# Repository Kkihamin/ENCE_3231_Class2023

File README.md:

# ENCE_3231_Class2023 Phase D

## Introduction of Project
  The inspiration initially for the final project in this class was I was researching on the internet for ideas on projects that are beneficial in my daily life and achievable in three weeks even if there are complications during the process of the project. Then, I came across a fridge alarm circuit on the internet and I thought this was a good project idea that was not too difficult to achieve in three weeks and this project could be meaningful because if someone forgets to close there refridgerator this circuit could tell them through a sound from a buzzer that the refridgerator door is open.
  The original circuit that internet provided which is given below was way too complex for three weeks because there were some challenges of implementing the original circuit. First, it was implemented on Arduino instead of the stm32cubeide that I needed to use. Second, there were two timer ic chips which it would take some time to understand to incorporate in the ide. Third, the 9 volts needed for the ic chips are not able to be provided by the voltage on the stm32F4 discovery board and I did not know how to interface a battery with the STM32F4 discovery board. This is why I made the project simplier to be able to accomplish the project in three weeks.

## Components

| Components | Quantity |
| ------------- | ------------- |
| AST-030C0MR-R passive Buzzer  | 1  |
| Green LED  | 1  |
| 100 ohm resistor  | 1 |
| STM32F discovery board  | 1  |
| HRC-SR501 Motion Sensor | 1  |

The table above shows all the components used in my final project which is the Fridge Alarm system.

## Schematic
Below is the Schematic and flowchart of the code on paper the only thing that needs to change is the buzzer should be using pin PE9 instead of PB11 and there is no Timer2:

The Schematic of the Fridge Alarm is shown in Kicad below:

## Shield Development
Below I have included a picture of the shield for my fridge door alarm routed and in 3-D view. The only thing is that I created my own library for the HRC-SR501 motion sensor so the pins on the custom component in my custom library and at first I didn't know why they were not routing and figured out that the pins needed pin numbers so they can actually route.

## Software Development
The main code for the Fridge door alarm is listed below

'''int main(void){
    HAL_Init();
    SystemClock_Config();
     MX_GPIO_Init();
     MX_TIM1_Init();
     MX_TIM2_Init();
     MX_BUZZER_Init();
     while (1)
     {

	  if(gISR_Flag_PIR){
		  HAL_GPIO_WritePin(gLED_PIN_PORT, gLED_PIN, SET); // Turn on LED
		 // HAL_GPIO_WritePin(BUZZER_PIN_PORT, BUZZER_PIN, SET); // Turn on buzzer
		  HAL_TIM_PWM_Start(&htim1, gBUZZER_TIM_CHANNEL);
		  HAL_Delay(1000); // Delay for 1 second
		  //HAL_GPIO_WritePin(BUZZER_PIN_PORT, BUZZER_PIN, RESET); // Turn off buzzer
		  HAL_TIM_PWM_Stop(&htim1, gBUZZER_TIM_CHANNEL);
		  HAL_GPIO_WritePin(gLED_PIN_PORT, gLED_PIN, RESET); // Turn off LED
		  gISR_Flag_PIR = 0; // Reset the motion detection flag
	  }

      }
}'''

## Demonstration
Below is a image and video recording of the Fridge door alarm being demonstrated on a breadboard that when the motion sensor detects motion the Green LED lights up and the buzzer sounds

## Future Developments
This project can definitely be developed further to be more efficient and accurate because my current demonstration is not the best cause the environment affects the motion sensor and makes it adapt and unless the white part of the ensor is completely covered to limit the range it will not be as accurate.

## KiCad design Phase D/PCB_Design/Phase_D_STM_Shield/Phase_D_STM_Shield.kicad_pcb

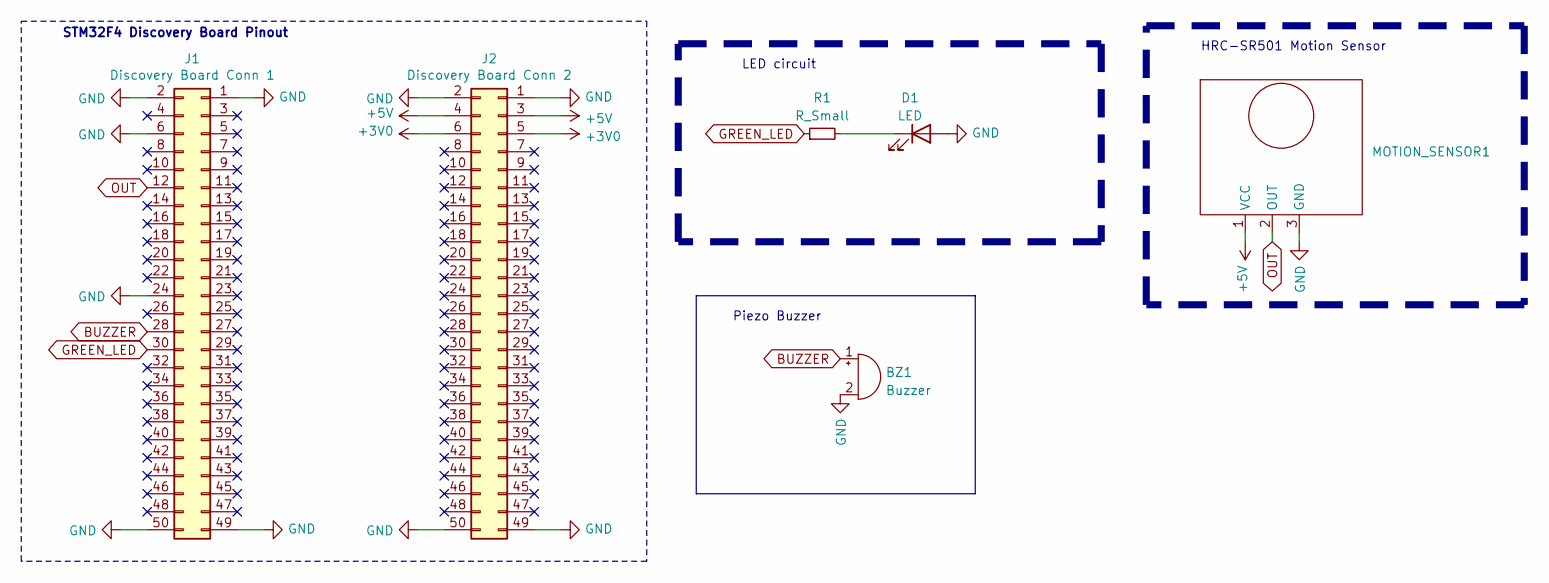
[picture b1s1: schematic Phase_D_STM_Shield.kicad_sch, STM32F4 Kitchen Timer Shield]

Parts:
BZ1: Buzzer; MagneticBuzzer_PUI_AT-0927-TT-6-R
D1: LED; LED_0603_1608Metric
J1: Discovery Board Conn 1; PinSocket_2x25_P2.54mm_Vertical
J2: Discovery Board Conn 2; PinSocket_2x25_P2.54mm_Vertical
MOTION_SENSOR1: PinSocket_1x03_P2.54mm_Vertical
R1: R_Small; R_0603_1608Metric

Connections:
+3V0: J2.5, J2.6
+5V: J2.3, J2.4, MOTION_SENSOR1.1 (VCC)
BUZZER: BZ1.1 (-), J1.28
GND: BZ1.2 (+), D1.2 (A), J1.1, J1.2, J1.6, J1.24, J1.49, J1.50, J2.1, J2.2, J2.49, J2.50, MOTION_SENSOR1.3 (GND)
GREEN_LED: J1.30, R1.1
unnamed: D1.1 (K), R1.2
OUT: J1.12, MOTION_SENSOR1.2 (OUT)

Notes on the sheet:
LED circuit
Piezo Buzzer
HRC-SR501 Motion Sensor
STM32F4 Discovery Board Pinout

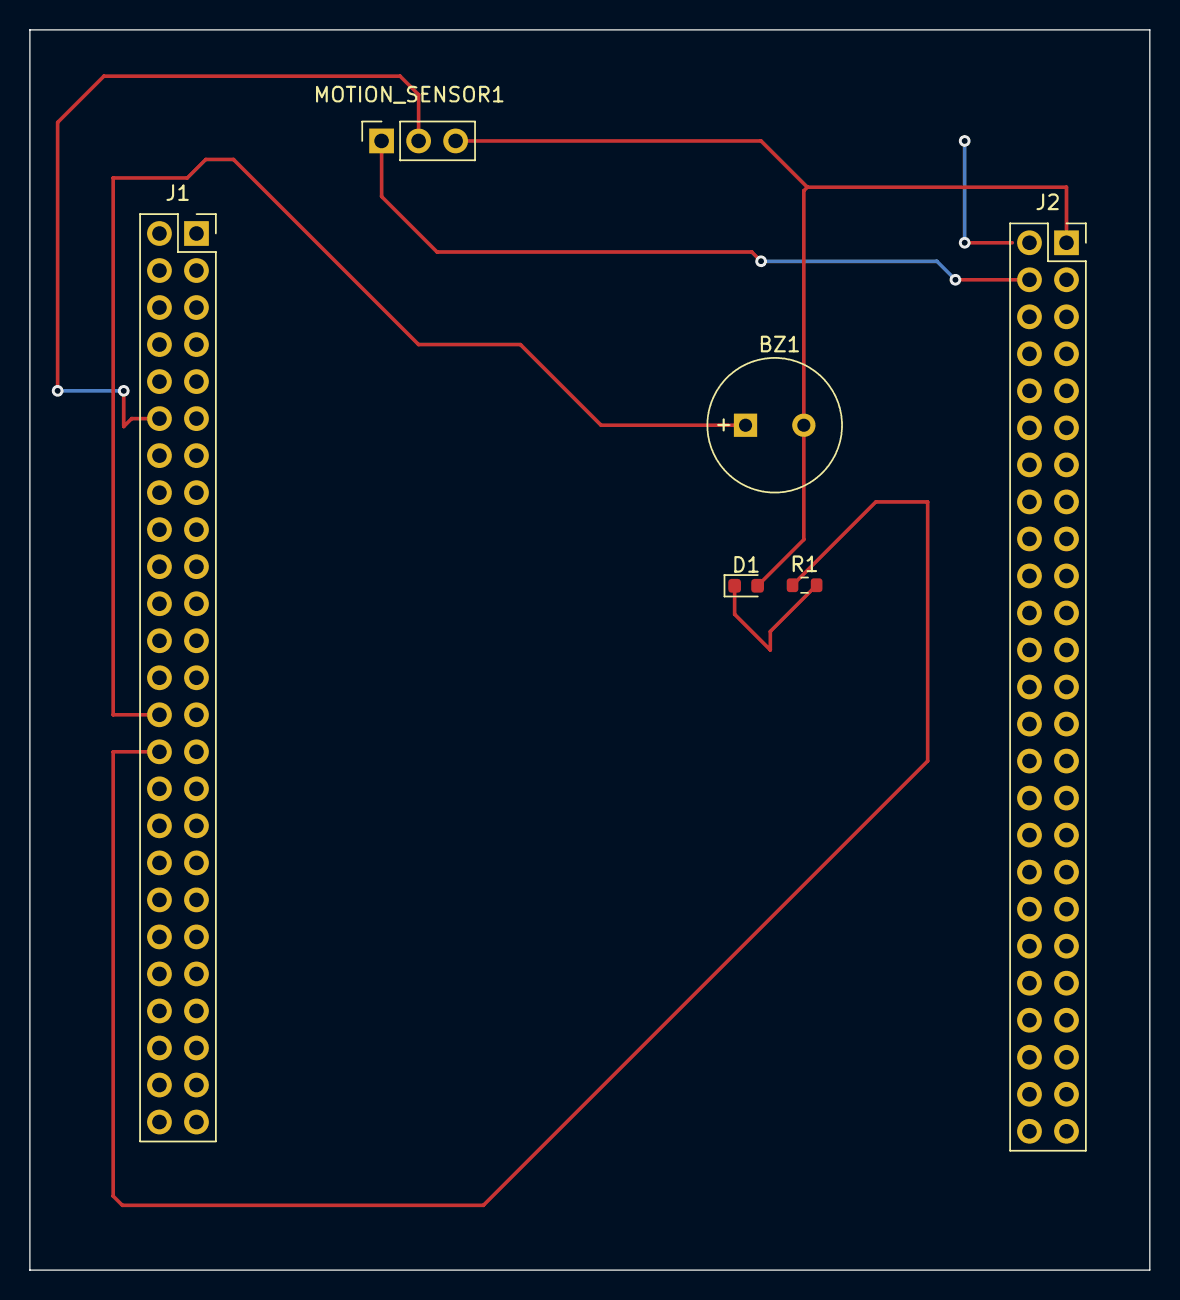
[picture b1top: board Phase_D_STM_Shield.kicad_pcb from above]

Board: 2 copper layers, 76.8 x 85.1 mm, 6 parts (0 on the bottom side), 7 nets.

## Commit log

2023-05-05 All Phases
2023-05-05 Phase B
2023-05-31 Initial work for final project
2023-05-31 datasheet for buzzer
2023-05-31 Hardware implementation of project
2023-05-31 edit
2023-06-01 Edits
2023-06-01 demonstration of the video
2023-06-01 code edit
2023-06-01 Demonstration
2023-06-01 Phase B edited and final report for phase B edited
